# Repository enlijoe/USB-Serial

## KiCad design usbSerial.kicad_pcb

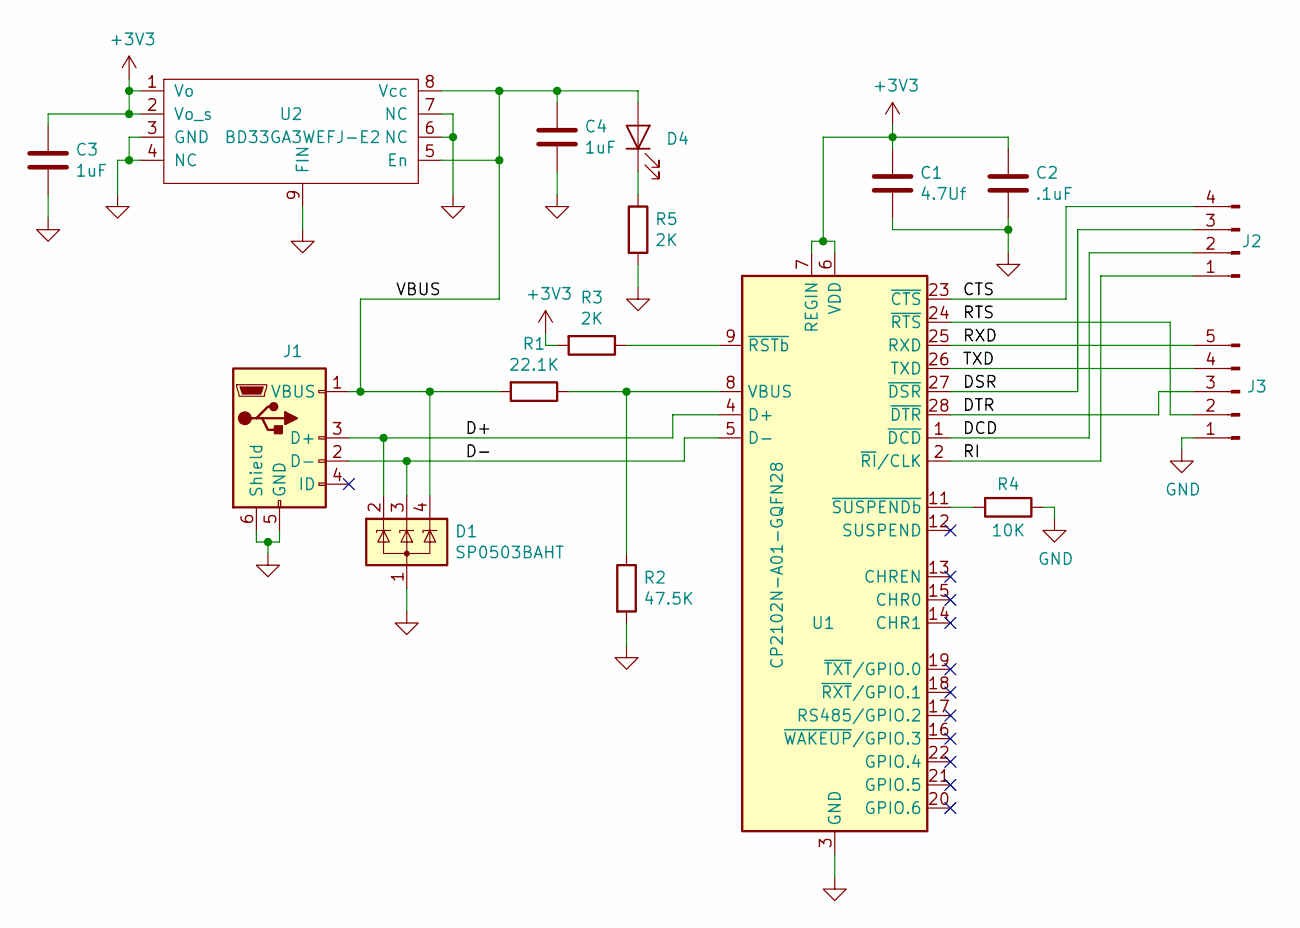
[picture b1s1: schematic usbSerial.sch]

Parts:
C1: 4.7Uf; C_0603_1608Metric; Mouser 187-CL10A475KP8NNNC
C2: .1uF; C_0603_1608Metric; Mouser 80-C0805C104K5R
C3, C4: 1uF; C_0603_1608Metric; Mouser 80-C0603C105K8PLR
D1: SP0503BAHT; SOT-143; Mouser 576-SP0503BAHTG
D4: LED; LED_0603_1608Metric; Mouser 710-155060SS75300
J1: USB_B_Micro; USB_Micro-B_Amphenol_10118194-0011LF_Horizontal; Mouser 649-10118194-0011LF
J2: Conn_01x04_Male; PinHeader_1x04_P2.54mm_Vertical; Mouser 538-87891-4006
J3: Conn_01x05_Male; PinHeader_1x05_P2.54mm_Vertical; Mouser 538-87891-4006
R1: 22.1K; R_0603_1608Metric; Mouser 603-RC0603FR-1022K1L
R2: 47.5K; R_0603_1608Metric; Mouser 755-SFR03EZPF4752
R3, R5: 2K; R_0603_1608Metric; Mouser 667-ERJ-3EKF2001V
R4: 10K; R_0603_1608Metric; Mouser 667-ERJ-3EKF1002V
U1: CP2102N-A01-GQFN28; QFN-28-1EP_5x5mm_P0.5mm_EP3.35x3.35mm; Mouser 634-CP2102NA02GQFN28
U2: BD33GA3WEFJ-E2; HTSOP-8-1EP_3.9x4.9mm_P1.27mm_EP2.4x3.2mm; Mouser 755-BD33GA3WEFJ-E2

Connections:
+3V3: C1.1, C2.1, C3.1, R3.2, U1.6 (VDD), U1.7 (REGIN), U2.1 (Vo), U2.2 (Vo_s)
/CTS: J2.4, U1.23 (~CTS)
/D+: D1.2 (K), J1.3 (D+), U1.4 (D+)
/D-: D1.3 (K), J1.2 (D-), U1.5 (D-)
/DCD: J2.2, U1.1 (~DCD)
/DSR: J2.3, U1.27 (~DSR)
/DTR: J3.3, U1.28 (~DTR)
/RI: J2.1, U1.2 (~RI~/CLK)
/RTS: J3.2, U1.24 (~RTS)
/RXD: J3.5, U1.25 (RXD)
/TXD: J3.4, U1.26 (TXD)
/VBUS: C4.1, D1.4 (K), D4.2 (A), J1.1 (VBUS), R1.2, U2.5 (En), U2.8 (Vcc)
GND: C1.2, C2.2, C3.2, C4.2, D1.1 (A), J1.5 (GND), J1.6 (Shield), J3.1, R2.2, R4.1, R5.2, U1.3 (GND), U1.29 (GND), U2.3 (GND), U2.4 (NC), U2.6 (NC), U2.7 (NC), U2.9 (FIN)
unnamed: D4.1 (K), R5.1
unnamed: R1.1, R2.1, U1.8 (VBUS)
unnamed: R3.1, U1.9 (~RSTb)
unnamed: R4.2, U1.11 (~SUSPENDb)

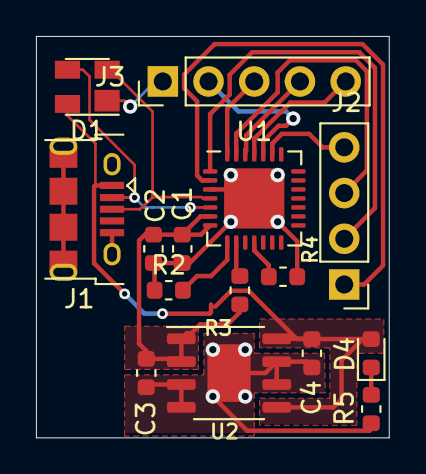
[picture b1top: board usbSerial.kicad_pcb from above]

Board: 2 copper layers, 19.6 x 22.3 mm, 15 parts (0 on the bottom side), 17 nets.

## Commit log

2020-10-30 Inital project
    Inital project
